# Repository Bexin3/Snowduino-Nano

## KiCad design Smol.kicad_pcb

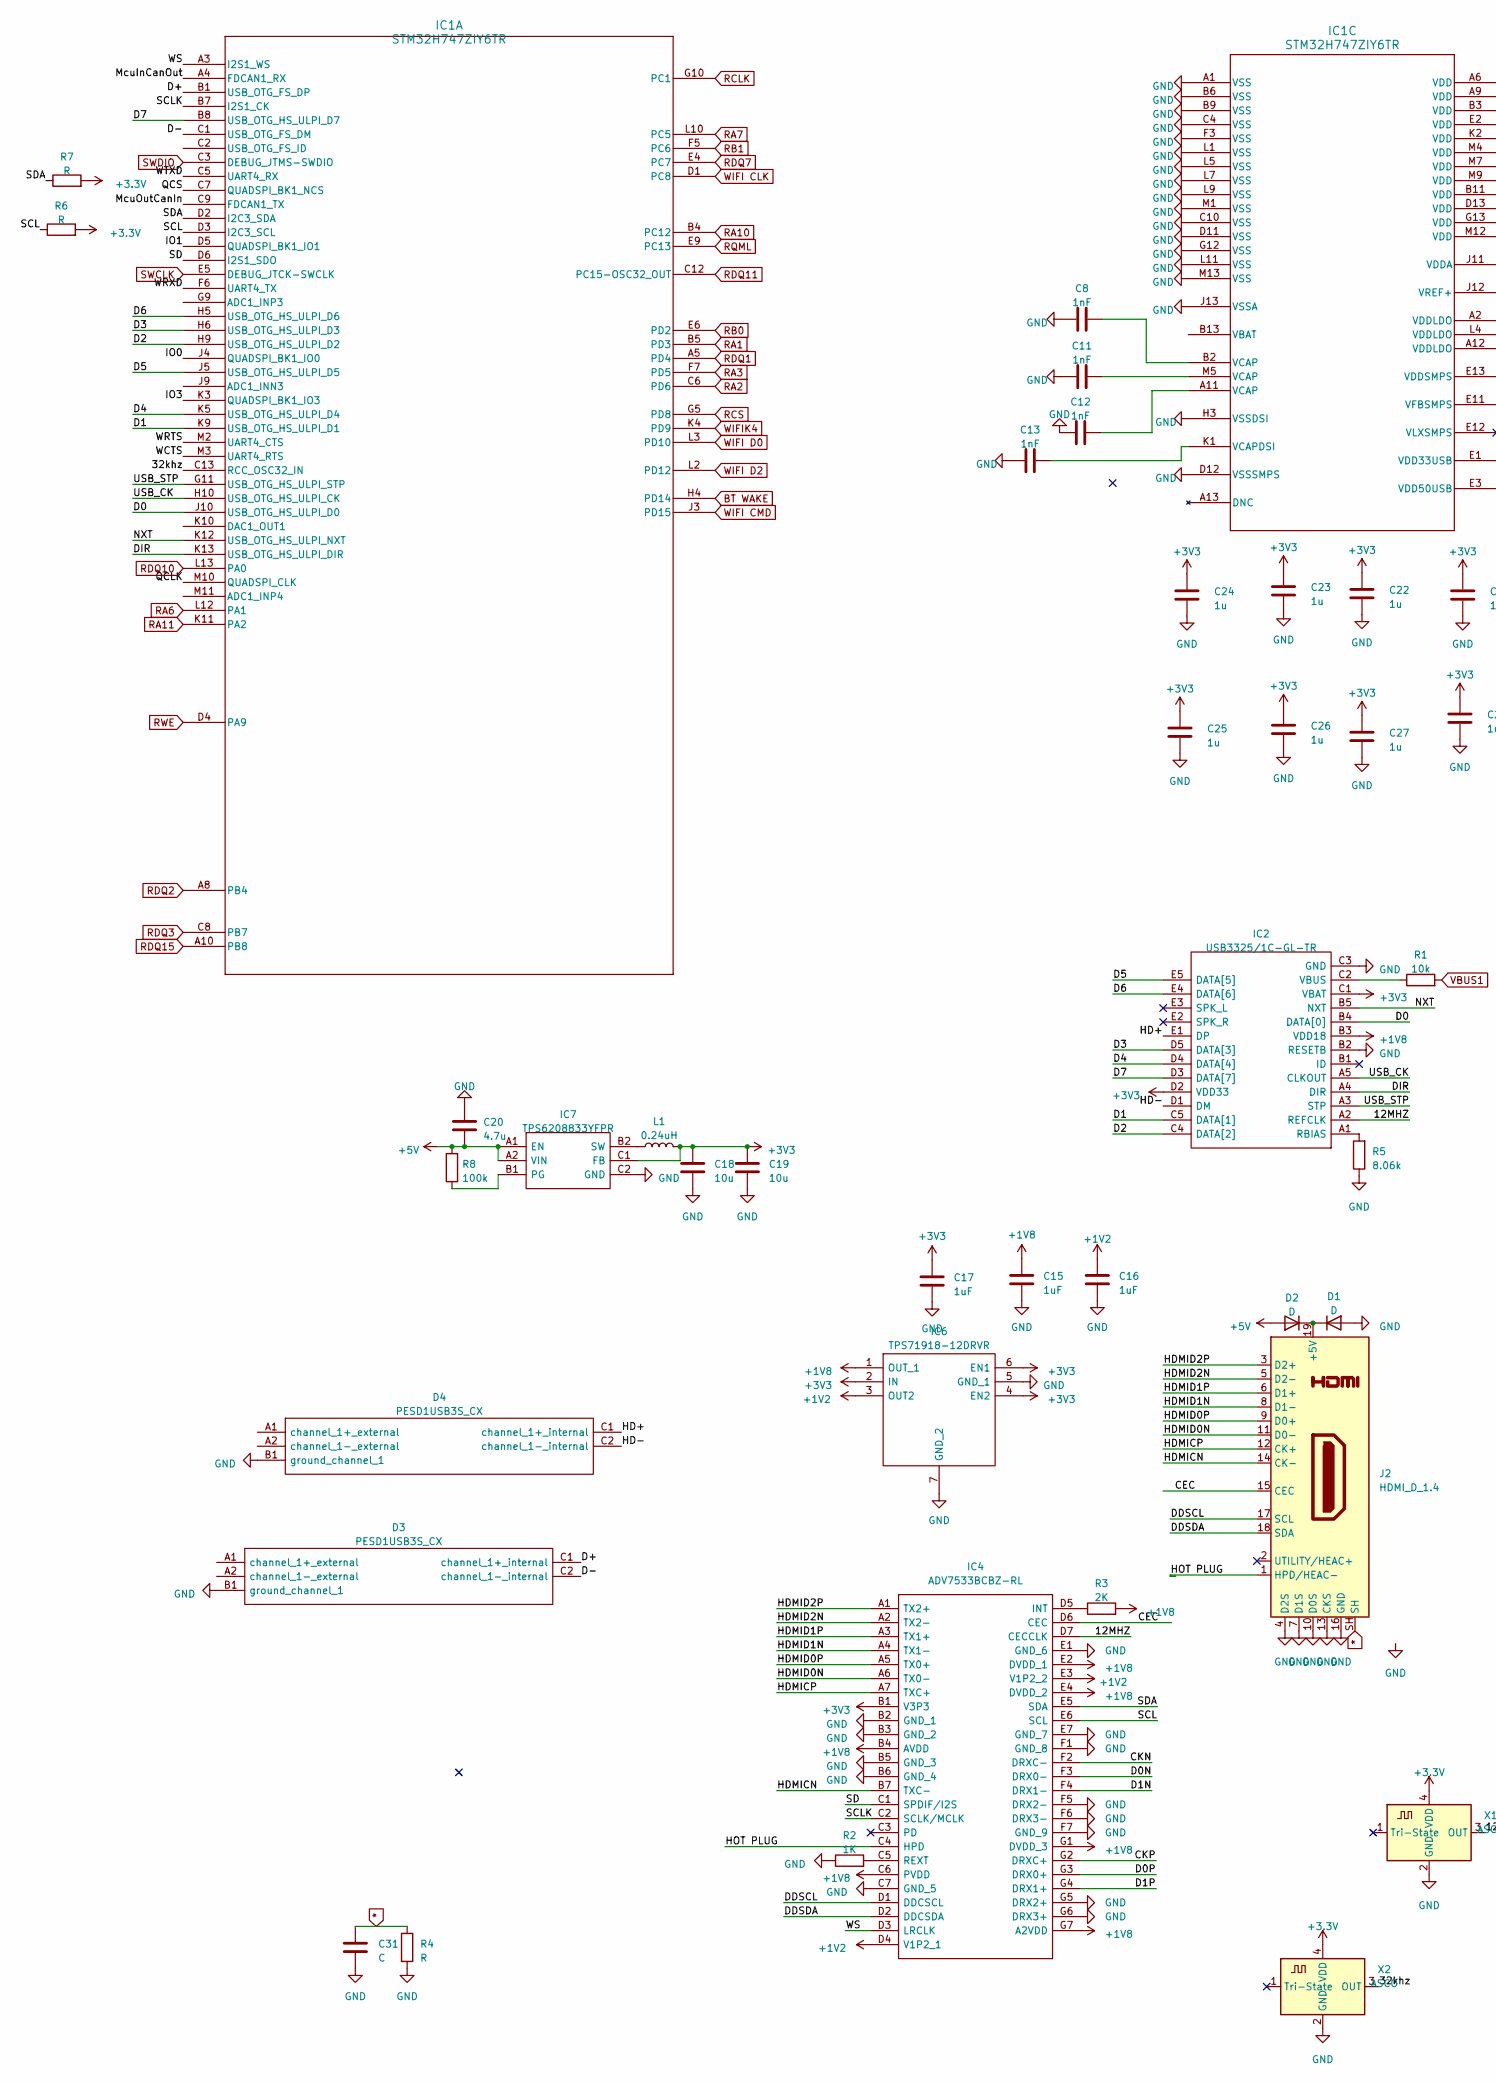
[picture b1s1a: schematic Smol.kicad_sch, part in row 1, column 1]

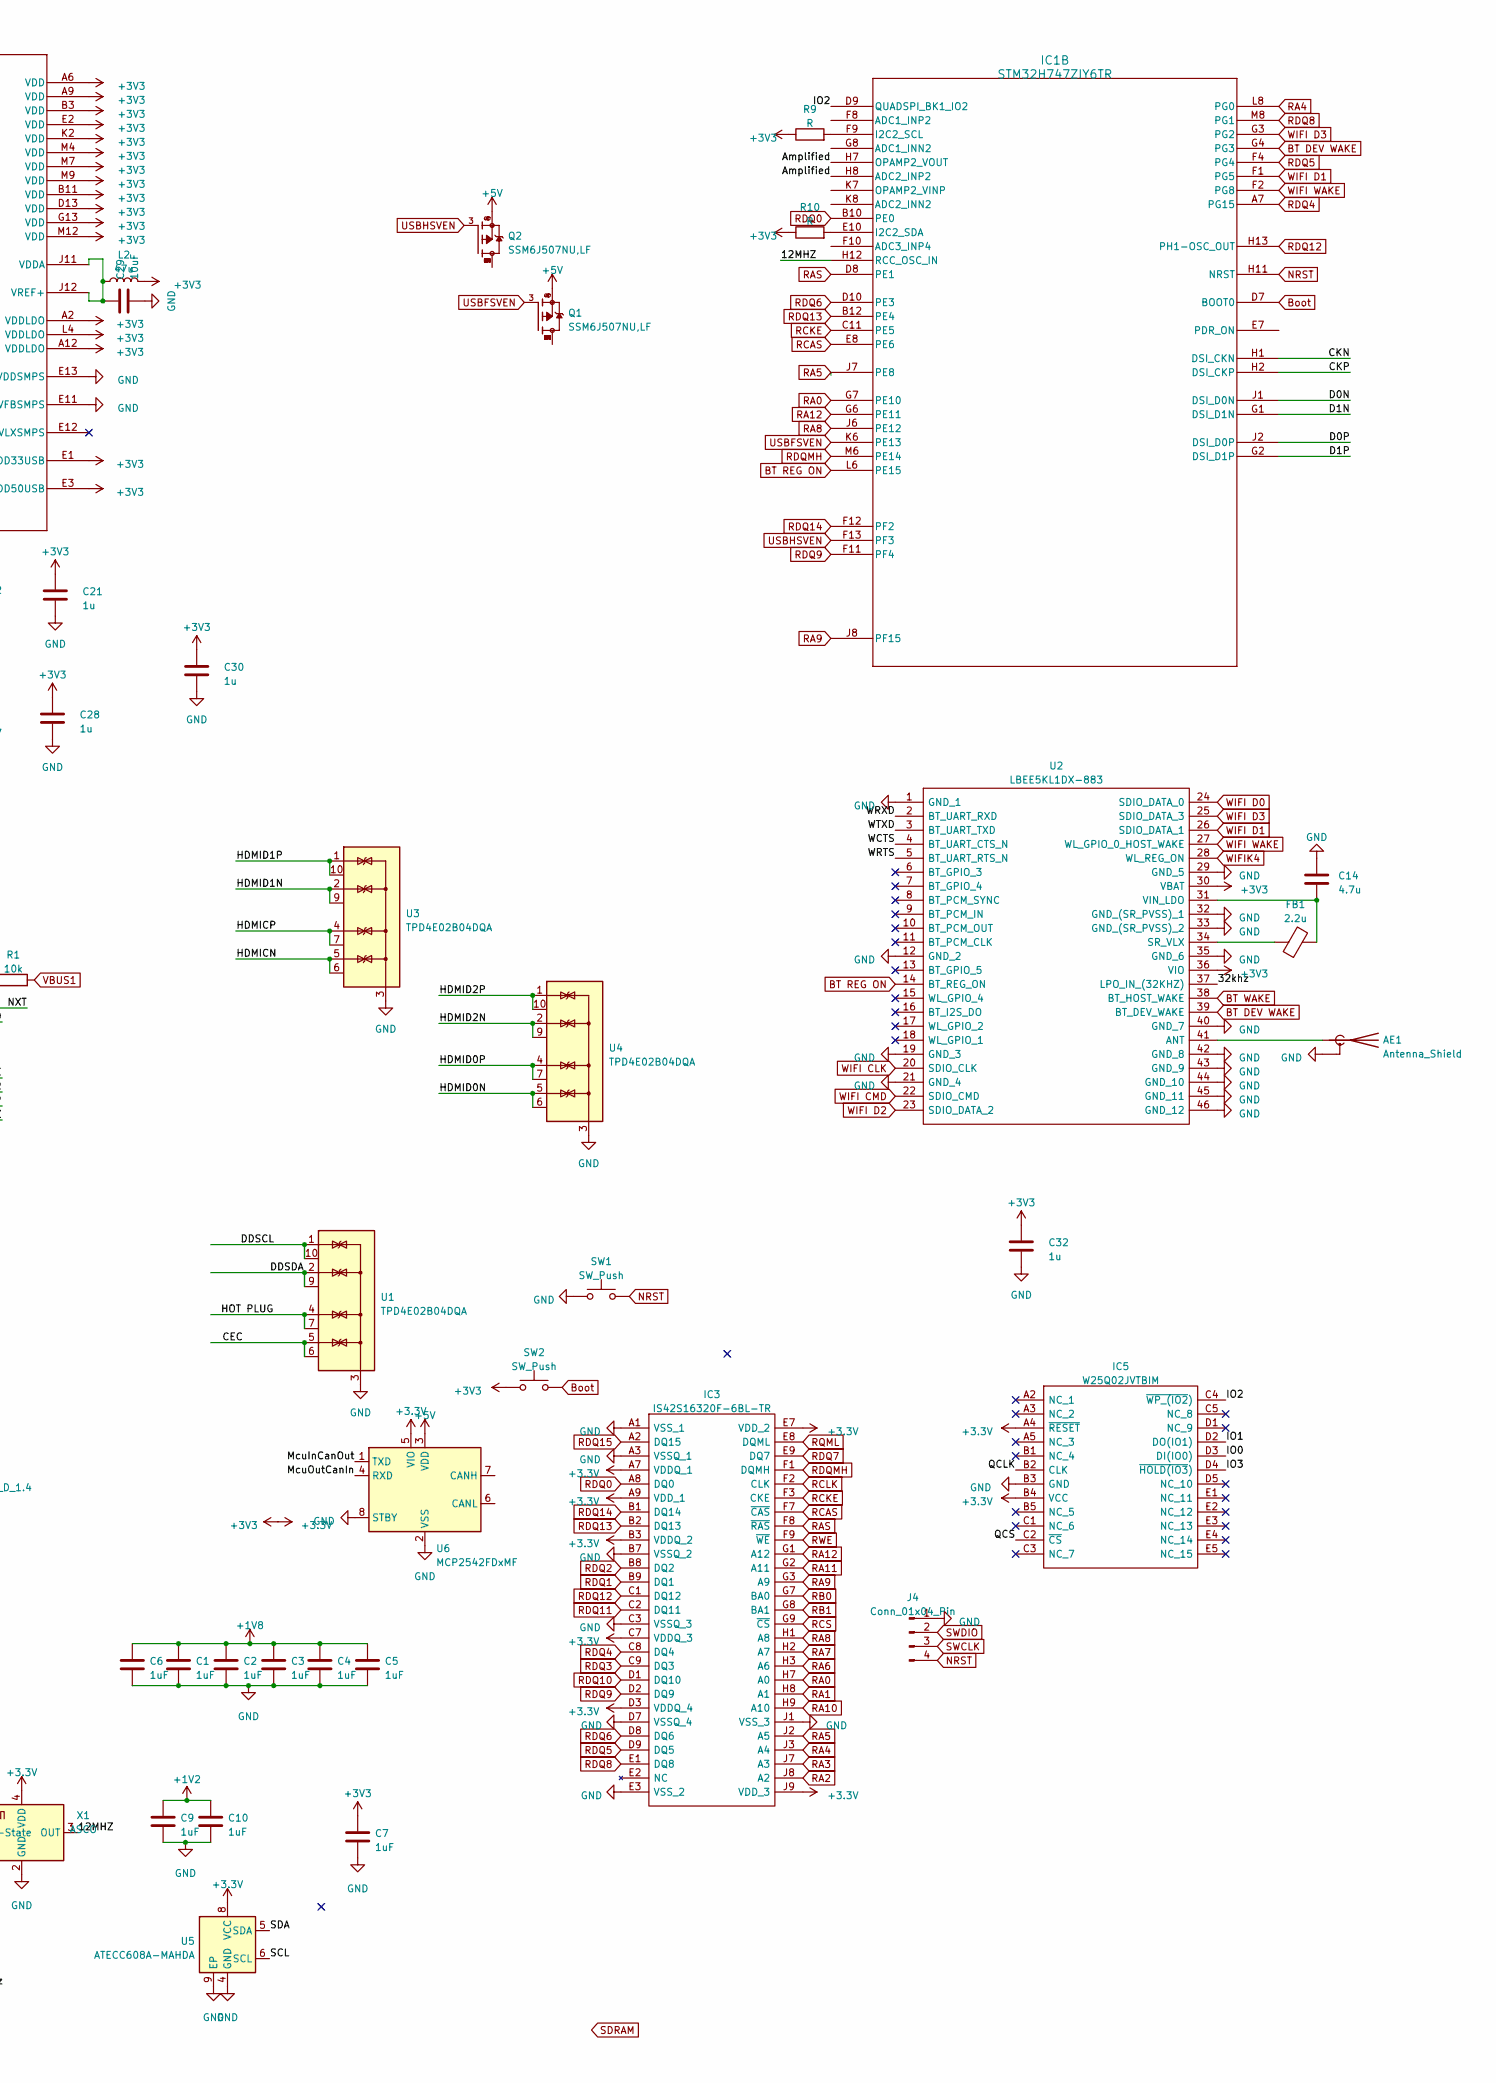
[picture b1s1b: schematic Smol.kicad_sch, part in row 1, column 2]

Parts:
AE1: Antenna_Shield; U.FL_Hirose_U.FL-R-SMT-1_Vertical
C1, C2, C3, C4, C5, C6, C7, C9, C10, C15, C16, C17: 1uF; C_0402_1005Metric
C8, C11, C12, C13: 1nF; C_0402_1005Metric
C14, C20: 4.7u; C_0402_1005Metric
C18, C19: 10u; C_0402_1005Metric
C21, C22, C23, C24, C25, C26, C27, C28, C30, C32: 1u; C_0402_1005Metric
C29: 10uF; C_0402_1005Metric
C31: C; C_0402_1005Metric
D1, D2: D; D_0402_1005Metric
D3, D4: PESD1USB3S_CX; PESD1USB3BCX; Manufacturer_Part_Number PESD1USB3S/CX; Mouser Part Number 771-PESD1USB3S/CX
FB1: 2.2u; L_0402_1005Metric
IC1: STM32H747ZIY6TR; BGA156C35P13X12_496X464X58
IC2: USB3325/1C-GL-TR; BGA25C40P5X5_197X197X62; Manufacturer_Part_Number USB3322C-GL-TR; Mouser Part Number 886-USB3322C-GL-TR
IC3: IS42S16320F-6BL-TR; BGA54C80P9X9_800X800X120; Manufacturer_Part_Number IS42S16160J-7BLI; Mouser Part Number 870-42S16160J7BLI
IC4: ADV7533BCBZ-RL; BGA49C50P7X7_346X346X66; Manufacturer_Part_Number ADV7533BCBZ-RL; Mouser Part Number 584-ADV7533BCBZ-R
IC5: W25Q02JVTBIM; BGA24C100P5X5_600X800X120; Manufacturer_Part_Number W25Q02JVTBIM; Mouser Part Number 454-W25Q02JVTBIM
IC6: TPS71918-12DRVR; SON65P200X200X80-7N; Manufacturer_Part_Number TPS71918-12DRVR; Mouser Part Number 595-TPS71918-12DRVR
IC7: TPS6208833YFPR; BGA6C40P2X3_80X120X50; Manufacturer_Part_Number TPS6208833YFPR; Mouser Part Number 595-TPS6208833YFPR
J2: HDMI_D_1.4; HDMI_Micro-D_Molex_46765-0x01
J4: Conn_01x04_Pin; PinHeader_1x04_P1.27mm_Vertical
L1: 0.24uH; L_0402_1005Metric
L2: 47u; L_0402_1005Metric
Q1, Q2: SSM6J507NU,LF; TRANS_SSM6J507NU,LF; PARTREV 2.0
R1: 10k; R_0402_1005Metric
R2: 1K; R_0402_1005Metric
R3: 2K; R_0402_1005Metric
R4, R6, R7, R9, R10: R; R_0402_1005Metric
R5: 8.06k; R_0402_1005Metric
R8: 100k; R_0402_1005Metric
SW1, SW2: SW_Push; NanoT160AS
U1, U3, U4: TPD4E02B04DQA; USON-10_2.5x1.0mm_P0.5mm
U2: LBEE5KL1DX-883; LBEE5KL1DX; Manufacturer_Part_Number LBEE5KL1DX-883; Mouser Part Number 81-LBEE5KL1DX-883
U5: ATECC608A-MAHDA; DFN-8-1EP_3x2mm_P0.5mm_EP1.3x1.5mm
U6: MCP2542FDxMF; DFN-8-1EP_3x2mm_P0.5mm_EP1.75x1.45mm
X1, X2: ASCO; Oscillator_SMD_Abracon_ASCO-4Pin_1.6x1.2mm

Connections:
*: C31.1, J2.SH, R4.1
+1V2: C9.1, C10.1, C16.1, IC4.D4 (V1P2_1), IC4.E3 (V1P2_2), IC6.3 (OUT2)
+1V8: C1.1, C2.1, C3.1, C4.1, C5.1, C6.1, C15.1, IC2.B3 (VDD18), IC4.B4 (AVDD), IC4.C6 (PVDD), IC4.E2 (DVDD_1), IC4.E4 (DVDD_2), IC4.G1 (DVDD_3), IC4.G7 (A2VDD), IC6.1 (OUT_1), R3.2
+3.3V: C7.1, C17.1, C18.1, C19.1, C21.1, C22.1, C23.1, C24.1, C25.1, C26.1, C27.1, C28.1, C30.1, C32.1, IC1.A2 (VDDLDO), IC1.A6 (VDD), IC1.A9 (VDD), IC1.A12 (VDDLDO), IC1.B3 (VDD), IC1.B11 (VDD), IC1.D13 (VDD), IC1.E1 (VDD33USB), IC1.E2 (VDD), IC1.E3 (VDD50USB), IC1.G13 (VDD), IC1.K2 (VDD), IC1.L4 (VDDLDO), IC1.M4 (VDD), IC1.M7 (VDD), IC1.M9 (VDD), IC1.M12 (VDD), IC2.C1 (VBAT), IC2.D2 (VDD33), IC3.A7 (VDDQ_1), IC3.A9 (VDD_1), IC3.B3 (VDDQ_2), IC3.C7 (VDDQ_3), IC3.D3 (VDDQ_4), IC3.E7 (VDD_2), IC3.J9 (VDD_3), IC4.B1 (V3P3), IC5.A4 (~RESET), IC5.B4 (VCC), IC6.2 (IN), IC6.4 (EN2), IC6.6 (EN1), IC7.C1 (FB), L1.2, L2.2, R6.2, R7.2, R9.1, R10.1, SW2.1, U2.30 (VBAT), U2.36 (VIO), U5.8 (VCC), U6.5 (VIO), X1.4 (VDD), X2.4 (VDD)
+5V: C20.2, D2.2 (A), IC7.A1 (EN), IC7.A2 (VIN), Q1.4, Q1.8, Q2.4, Q2.8, R8.2, U6.3 (VDD)
/12MHZ: IC1.H12 (RCC_OSC_IN), IC2.A2 (REFCLK), IC4.D7 (CECCLK), X1.3 (OUT)
/32khz: IC1.C13 (RCC_OSC32_IN), U2.37 (LPO_IN_(32KHZ)), X2.3 (OUT)
/Amplified: IC1.H7 (OPAMP2_VOUT), IC1.H8 (ADC2_INP2)
/CEC: IC4.D6 (CEC), J2.15 (CEC), U1.5 (IO4), U1.6 (NC)
/CKN: IC1.H1 (DSI_CKN), IC4.F2 (DRXC-)
/CKP: IC1.H2 (DSI_CKP), IC4.G2 (DRXC+)
/D0: IC1.J10 (USB_OTG_HS_ULPI_D0), IC2.B4 (DATA[0])
/D0N: IC1.J1 (DSI_D0N), IC4.F3 (DRX0-)
/D0P: IC1.J2 (DSI_D0P), IC4.G3 (DRX0+)
/D1: IC1.K9 (USB_OTG_HS_ULPI_D1), IC2.C5 (DATA[1])
/D1N: IC1.G1 (DSI_D1N), IC4.F4 (DRX1-)
/D1P: IC1.G2 (DSI_D1P), IC4.G4 (DRX1+)
/D2: IC1.H9 (USB_OTG_HS_ULPI_D2), IC2.C4 (DATA[2])
/D3: IC1.H6 (USB_OTG_HS_ULPI_D3), IC2.D5 (DATA[3])
/D4: IC1.K5 (USB_OTG_HS_ULPI_D4), IC2.D4 (DATA[4])
/D5: IC1.J5 (USB_OTG_HS_ULPI_D5), IC2.E5 (DATA[5])
/D6: IC1.H5 (USB_OTG_HS_ULPI_D6), IC2.E4 (DATA[6])
/D7: IC1.B8 (USB_OTG_HS_ULPI_D7), IC2.D3 (DATA[7])
/D+: D3.C1 (channel_1+_internal), IC1.B1 (USB_OTG_FS_DP)
/D-: D3.C2 (channel_1-_internal), IC1.C1 (USB_OTG_FS_DM)
/DDSCL: IC4.D1 (DDCSCL), J2.17 (SCL), U1.1 (IO1), U1.10 (NC)
/DDSDA: IC4.D2 (DDCSDA), J2.18 (SDA), U1.2 (IO2), U1.9 (NC)
/DIR: IC1.K13 (USB_OTG_HS_ULPI_DIR), IC2.A4 (DIR)
/HD+: D4.C1 (channel_1+_internal), IC2.E1 (DP)
/HD-: D4.C2 (channel_1-_internal), IC2.D1 (DM)
/HDMICN: IC4.B7 (TXC-), J2.14 (CK-), U3.5 (IO4), U3.6 (NC)
/HDMICP: IC4.A7 (TXC+), J2.12 (CK+), U3.4 (IO3), U3.7 (NC)
/HDMID0N: IC4.A6 (TX0-), J2.11 (D0-), U4.5 (IO4), U4.6 (NC)
/HDMID0P: IC4.A5 (TX0+), J2.9 (D0+), U4.4 (IO3), U4.7 (NC)
/HDMID1N: IC4.A4 (TX1-), J2.8 (D1-), U3.2 (IO2), U3.9 (NC)
/HDMID1P: IC4.A3 (TX1+), J2.6 (D1+), U3.1 (IO1), U3.10 (NC)
/HDMID2N: IC4.A2 (TX2-), J2.5 (D2-), U4.2 (IO2), U4.9 (NC)
/HDMID2P: IC4.A1 (TX2+), J2.3 (D2+), U4.1 (IO1), U4.10 (NC)
/HOT PLUG: IC4.C4 (HPD), J2.1 (HPD/HEAC-), U1.4 (IO3), U1.7 (NC)
/IO0: IC1.J4 (QUADSPI_BK1_IO0), IC5.D3 (DI(IO0))
/IO1: IC1.D5 (QUADSPI_BK1_IO1), IC5.D2 (DO(IO1))
/IO2: IC1.D9 (QUADSPI_BK1_IO2), IC5.C4 (~WP_(IO2))
/IO3: IC1.K3 (QUADSPI_BK1_IO3), IC5.D4 (~HOLD(IO3))
/McuInCanOut: IC1.A4 (FDCAN1_RX), U6.1 (TXD)
/McuOutCanIn: IC1.C9 (FDCAN1_TX), U6.4 (RXD)
/NXT: IC1.K12 (USB_OTG_HS_ULPI_NXT), IC2.B5 (NXT)
/QCLK: IC1.M10 (QUADSPI_CLK), IC5.B2 (CLK)
/QCS: IC1.C7 (QUADSPI_BK1_NCS), IC5.C2 (~CS)
/SCL: IC1.D3 (I2C3_SCL), IC4.E6 (SCL), R6.1, U5.6 (SCL)
/SCLK: IC1.B7 (I2S1_CK), IC4.C2 (SCLK/MCLK)
/SD: IC1.D6 (I2S1_SDO), IC4.C1 (SPDIF/I2S)
/SDA: IC1.D2 (I2C3_SDA), IC4.E5 (SDA), R7.1, U5.5 (SDA)
/USB_CK: IC1.H10 (USB_OTG_HS_ULPI_CK), IC2.A5 (CLKOUT)
/USB_STP: IC1.G11 (USB_OTG_HS_ULPI_STP), IC2.A3 (STP)
/WCTS: IC1.M3 (UART4_RTS), U2.4 (BT_UART_CTS_N)
/WRTS: IC1.M2 (UART4_CTS), U2.5 (BT_UART_RTS_N)
/WRXD: IC1.F6 (UART4_TX), U2.2 (BT_UART_RXD)
/WS: IC1.A3 (I2S1_WS), IC4.D3 (LRCLK)
/WTXD: IC1.C5 (UART4_RX), U2.3 (BT_UART_TXD)
BT DEV WAKE: IC1.G4 (PG3), U2.39 (BT_DEV_WAKE)
BT REG ON: IC1.L6 (PE15), U2.14 (BT_REG_ON)
BT WAKE: IC1.H4 (PD14), U2.38 (BT_HOST_WAKE)
Boot: IC1.D7 (BOOT0), SW2.2
GND: AE1.2 (Shield), C1.2, C2.2, C3.2, C4.2, C5.2, C6.2, C7.2, C8.1, C9.2, C10.2, C11.1, C12.1, C13.1, C14.1, C15.2, C16.2, C17.2, C18.2, C19.2, C20.1, C21.2, C22.2, C23.2, C24.2, C25.2, C26.2, C27.2, C28.2, C29.2, C30.2, C31.2, C32.2, D1.2 (A), D3.B1 (ground_channel_1), D4.B1 (ground_channel_1), IC1.A1 (VSS), IC1.B6 (VSS), IC1.B9 (VSS), IC1.C4 (VSS), IC1.C10 (VSS), IC1.D11 (VSS), IC1.D12 (VSSSMPS), IC1.E11 (VFBSMPS), IC1.E13 (VDDSMPS), IC1.F3 (VSS), IC1.G12 (VSS), IC1.H3 (VSSDSI), IC1.J13 (VSSA), IC1.L1 (VSS), IC1.L5 (VSS), IC1.L7 (VSS), IC1.L9 (VSS), IC1.L11 (VSS), IC1.M1 (VSS), IC1.M13 (VSS), IC2.B2 (RESETB), IC2.C3 (GND), IC3.A1 (VSS_1), IC3.A3 (VSSQ_1), IC3.B7 (VSSQ_2), IC3.C3 (VSSQ_3), IC3.D7 (VSSQ_4), IC3.E3 (VSS_2), IC3.J1 (VSS_3), IC4.B2 (GND_1), IC4.B3 (GND_2), IC4.B5 (GND_3), IC4.B6 (GND_4), IC4.C7 (GND_5), IC4.E1 (GND_6), IC4.E7 (GND_7), IC4.F1 (GND_8), IC4.F5 (DRX2-), IC4.F6 (DRX3-), IC4.F7 (GND_9), IC4.G5 (DRX2+), IC4.G6 (DRX3+), IC5.B3 (GND), IC6.5 (GND_1), IC6.7 (GND_2), IC7.C2 (GND), J2.4 (D2S), J2.7 (D1S), J2.10 (D0S), J2.13 (CKS), J2.16 (GND), J4.1, R2.1, R4.2, R5.1, SW1.1, U1.3 (G), U1.8 (G), U2.1 (GND_1), U2.12 (GND_2), U2.19 (GND_3), U2.21 (GND_4), U2.29 (GND_5), U2.32 (GND_(SR_PVSS)_1), U2.33 (GND_(SR_PVSS)_2), U2.35 (GND_6), U2.40 (GND_7), U2.42 (GND_8), U2.43 (GND_9), U2.44 (GND_10), U2.45 (GND_11), U2.46 (GND_12), U3.3 (G), U3.8 (G), U4.3 (G), U4.8 (G), U5.4 (GND), U5.9 (EP), U6.2 (VSS), U6.8 (STBY), U6.9 (VSS), X1.2 (GND), X2.2 (GND)
NRST: IC1.H11 (NRST), J4.4, SW1.2
unnamed: AE1.1 (A), U2.41 (ANT)
unnamed: C8.2, IC1.B2 (VCAP)
unnamed: C11.2, IC1.M5 (VCAP)
unnamed: C12.2, IC1.A11 (VCAP)
unnamed: D1.1 (K), D2.1 (K), J2.19 (+5V)
unnamed: IC1.F9 (I2C2_SCL), R9.2
unnamed: IC1.E10 (I2C2_SDA), R10.2
unnamed: C13.2, IC1.K1 (VCAPDSI)
unnamed: C29.1, IC1.J11 (VDDA), IC1.J12 (VREF+), L2.1
unnamed: IC2.A1 (RBIAS), R5.2
unnamed: IC2.C2 (VBUS), R1.1
unnamed: IC4.D5 (INT), R3.1
unnamed: IC4.C5 (REXT), R2.2
unnamed: IC7.B1 (PG), R8.1
unnamed: IC7.B2 (SW), L1.1
unnamed: Q1.1, Q1.2, Q1.5, Q1.6, Q1.7
unnamed: Q2.1, Q2.2, Q2.5, Q2.6, Q2.7
unnamed: FB1.1, U2.34 (SR_VLX)
unnamed: C14.2, FB1.2, U2.31 (VIN_LDO)
RA0: IC1.G7 (PE10), IC3.H7 (A0)
RA1: IC1.B5 (PD3), IC3.H8 (A1)
RA2: IC1.C6 (PD6), IC3.J8 (A2)
RA3: IC1.F7 (PD5), IC3.J7 (A3)
RA4: IC1.L8 (PG0), IC3.J3 (A4)
RA5: IC1.J7 (PE8), IC3.J2 (A5)
RA6: IC1.L12 (PA1), IC3.H3 (A6)
RA7: IC1.L10 (PC5), IC3.H2 (A7)
RA8: IC1.J6 (PE12), IC3.H1 (A8)
RA9: IC1.J8 (PF15), IC3.G3 (A9)
RA10: IC1.B4 (PC12), IC3.H9 (A10)
RA11: IC1.K11 (PA2), IC3.G2 (A11)
RA12: IC1.G6 (PE11), IC3.G1 (A12)
RAS: IC1.D8 (PE1), IC3.F8 (~RAS)
RB0: IC1.E6 (PD2), IC3.G7 (BA0)
RB1: IC1.F5 (PC6), IC3.G8 (BA1)
RCAS: IC1.E8 (PE6), IC3.F7 (~CAS)
RCKE: IC1.C11 (PE5), IC3.F3 (CKE)
RCLK: IC1.G10 (PC1), IC3.F2 (CLK)
RCS: IC1.G5 (PD8), IC3.G9 (~CS)
RDQ0: IC1.B10 (PE0), IC3.A8 (DQ0)
RDQ1: IC1.A5 (PD4), IC3.B9 (DQ1)
RDQ2: IC1.A8 (PB4), IC3.B8 (DQ2)
RDQ3: IC1.C8 (PB7), IC3.C9 (DQ3)
RDQ4: IC1.A7 (PG15), IC3.C8 (DQ4)
RDQ5: IC1.F4 (PG4), IC3.D9 (DQ5)
RDQ6: IC1.D10 (PE3), IC3.D8 (DQ6)
RDQ7: IC1.E4 (PC7), IC3.E9 (DQ7)
RDQ8: IC1.M8 (PG1), IC3.E1 (DQ8)
RDQ9: IC1.F11 (PF4), IC3.D2 (DQ9)
RDQ10: IC1.L13 (PA0), IC3.D1 (DQ10)
RDQ11: IC1.C12 (PC15-OSC32_OUT), IC3.C2 (DQ11)
RDQ12: IC1.H13 (PH1-OSC_OUT), IC3.C1 (DQ12)
RDQ13: IC1.B12 (PE4), IC3.B2 (DQ13)
RDQ14: IC1.F12 (PF2), IC3.B1 (DQ14)
RDQ15: IC1.A10 (PB8), IC3.A2 (DQ15)
RDQMH: IC1.M6 (PE14), IC3.F1 (DQMH)
RQML: IC1.E9 (PC13), IC3.E8 (DQML)
RWE: IC1.D4 (PA9), IC3.F9 (~WE)
SWCLK: IC1.E5 (DEBUG_JTCK-SWCLK), J4.3
SWDIO: IC1.C3 (DEBUG_JTMS-SWDIO), J4.2
USBFSVEN: IC1.K6 (PE13), Q1.3
USBHSVEN: IC1.F13 (PF3), Q2.3
VBUS1: R1.2
WIFI CLK: IC1.D1 (PC8), U2.20 (SDIO_CLK)
WIFI CMD: IC1.J3 (PD15), U2.22 (SDIO_CMD)
WIFI D0: IC1.L3 (PD10), U2.24 (SDIO_DATA_0)
WIFI D1: IC1.F1 (PG5), U2.26 (SDIO_DATA_1)
WIFI D2: IC1.L2 (PD12), U2.23 (SDIO_DATA_2)
WIFI D3: IC1.G3 (PG2), U2.25 (SDIO_DATA_3)
WIFI WAKE: IC1.F2 (PG8), U2.27 (WL_GPIO_0_HOST_WAKE)
WIFIK4: IC1.K4 (PD9), U2.28 (WL_REG_ON)

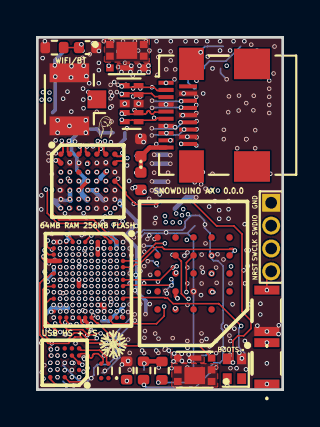
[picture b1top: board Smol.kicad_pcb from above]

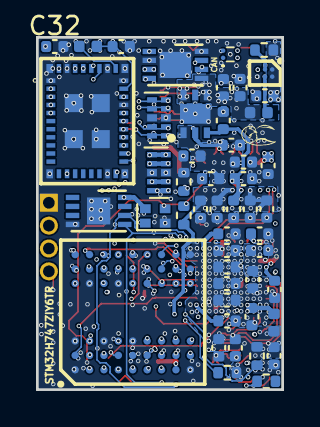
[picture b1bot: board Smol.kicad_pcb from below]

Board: 8 copper layers, 13.6 x 19.6 mm, 71 parts (50 on the bottom side), 135 nets.
